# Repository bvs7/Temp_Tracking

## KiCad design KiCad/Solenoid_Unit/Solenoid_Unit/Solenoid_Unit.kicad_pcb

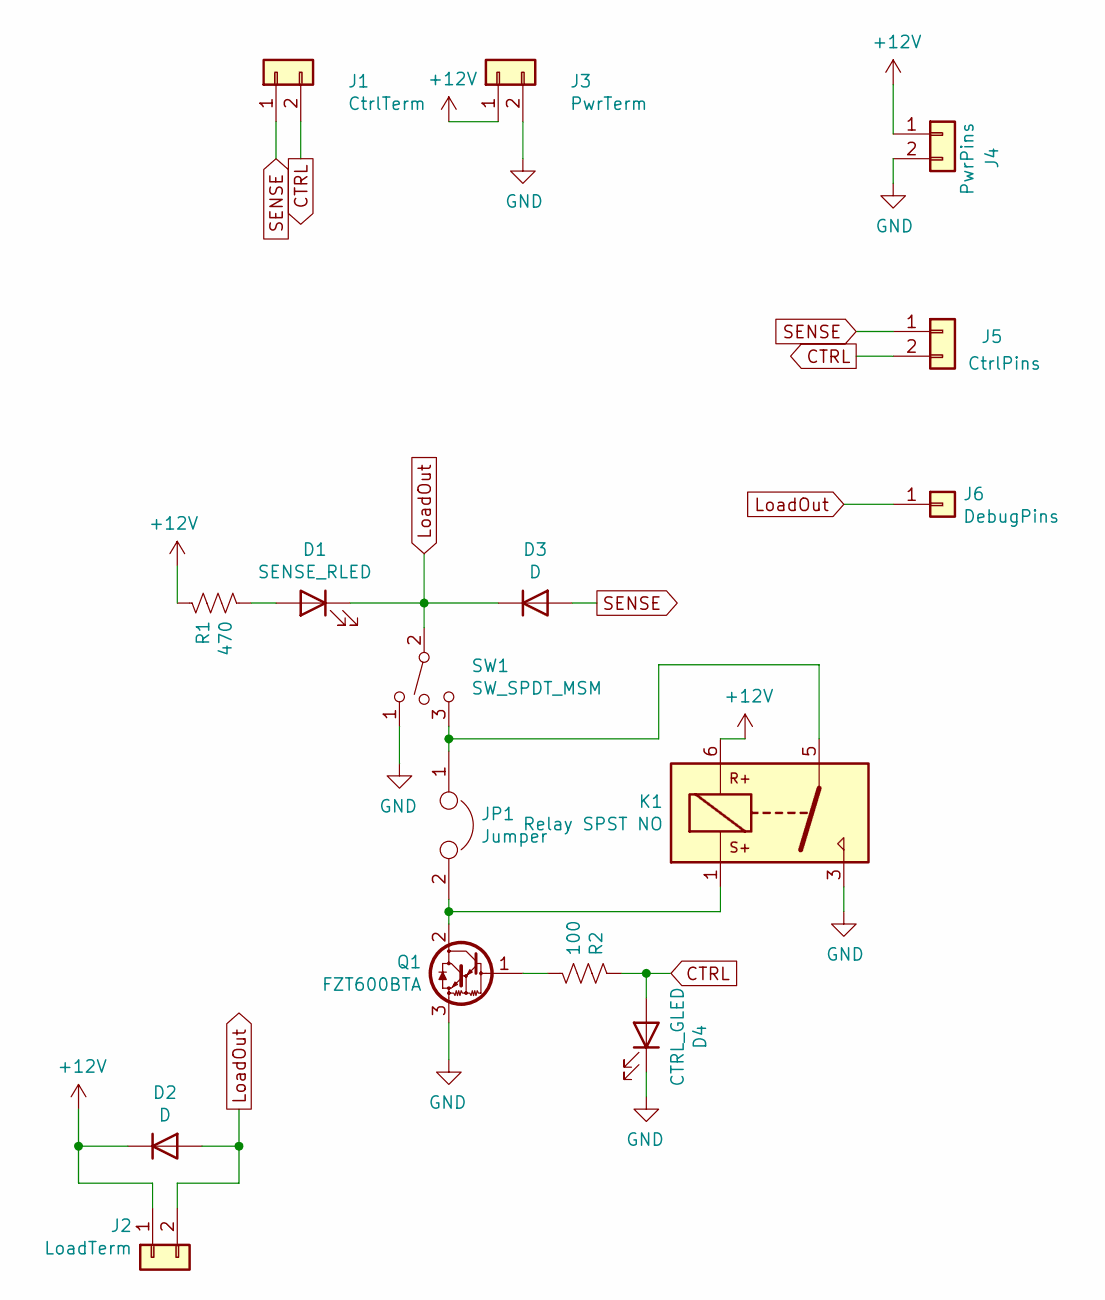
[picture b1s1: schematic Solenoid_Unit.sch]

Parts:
D1: SENSE_RLED; LED_0805_2012Metric
D2, D3: D; D_SOD-123F
D4: CTRL_GLED; LED_0603_1608Metric
J1: CtrlTerm; TerminalBlock_bornier-2_P5.08mm
J2: LoadTerm; TerminalBlock_bornier-2_P5.08mm
J3: PwrTerm; TerminalBlock_bornier-2_P5.08mm
J4: PwrPins; PinHeader_1x02_P2.54mm_Vertical
J5: CtrlPins; PinHeader_1x02_P2.54mm_Vertical
J6: DebugPins; PinHeader_1x01_P2.54mm_Vertical
JP1: Jumper; SolderJumper-2_P1.3mm_Bridged_Pad1.0x1.5mm
K1: Relay SPST NO; Relay_OMI-SH-112LM
Q1: FZT600BTA; SOT-223-3_TabPin2
R1: 470; R_0603_1608Metric
R2: 100; R_0603_1608Metric
SW1: SW_SPDT_MSM; SPDT_7101J1

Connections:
+12V: D2.1 (K), J2.1, J3.1, J4.1, K1.6, R1.1
CTRL: D4.2 (A), J1.2, J5.2, R2.1
GND: D4.1 (K), J3.2, J4.2, K1.3, Q1.3 (E), SW1.1
LoadOut: D1.1 (K), D2.2 (A), D3.1 (K), J2.2, J6.1, SW1.2
unnamed: D1.2 (A), R1.2
unnamed: JP1.1, K1.5, SW1.3
unnamed: JP1.2, K1.1, Q1.2 (C)
unnamed: Q1.1 (B), R2.2
SENSE: D3.2 (A), J1.1, J5.1

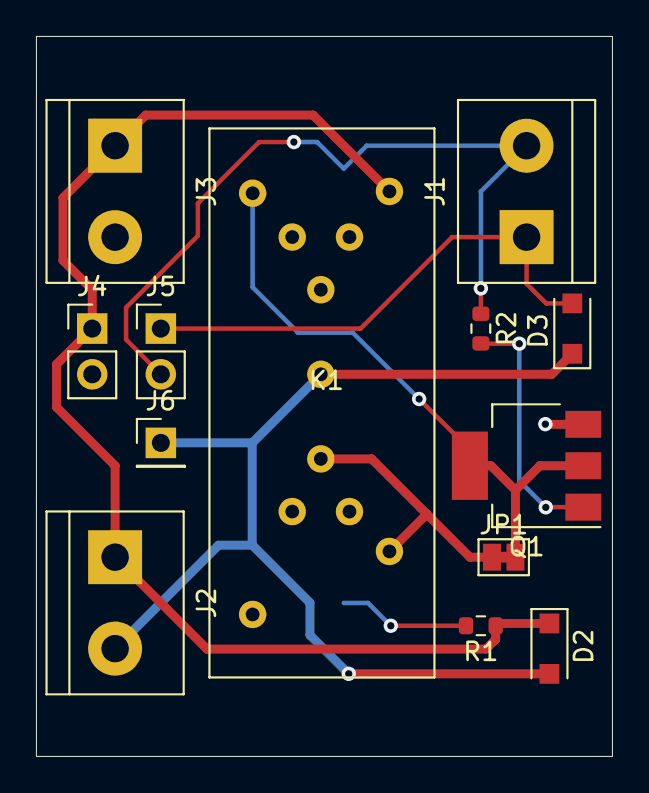
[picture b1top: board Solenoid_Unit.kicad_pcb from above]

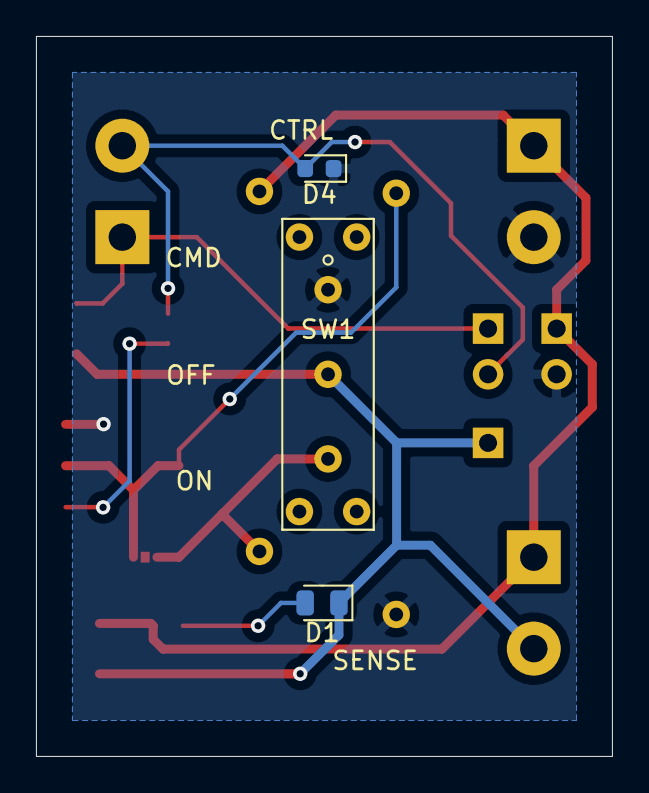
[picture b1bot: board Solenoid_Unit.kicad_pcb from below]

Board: 2 copper layers, 32.0 x 40.0 mm, 16 parts (3 on the bottom side), 9 nets.

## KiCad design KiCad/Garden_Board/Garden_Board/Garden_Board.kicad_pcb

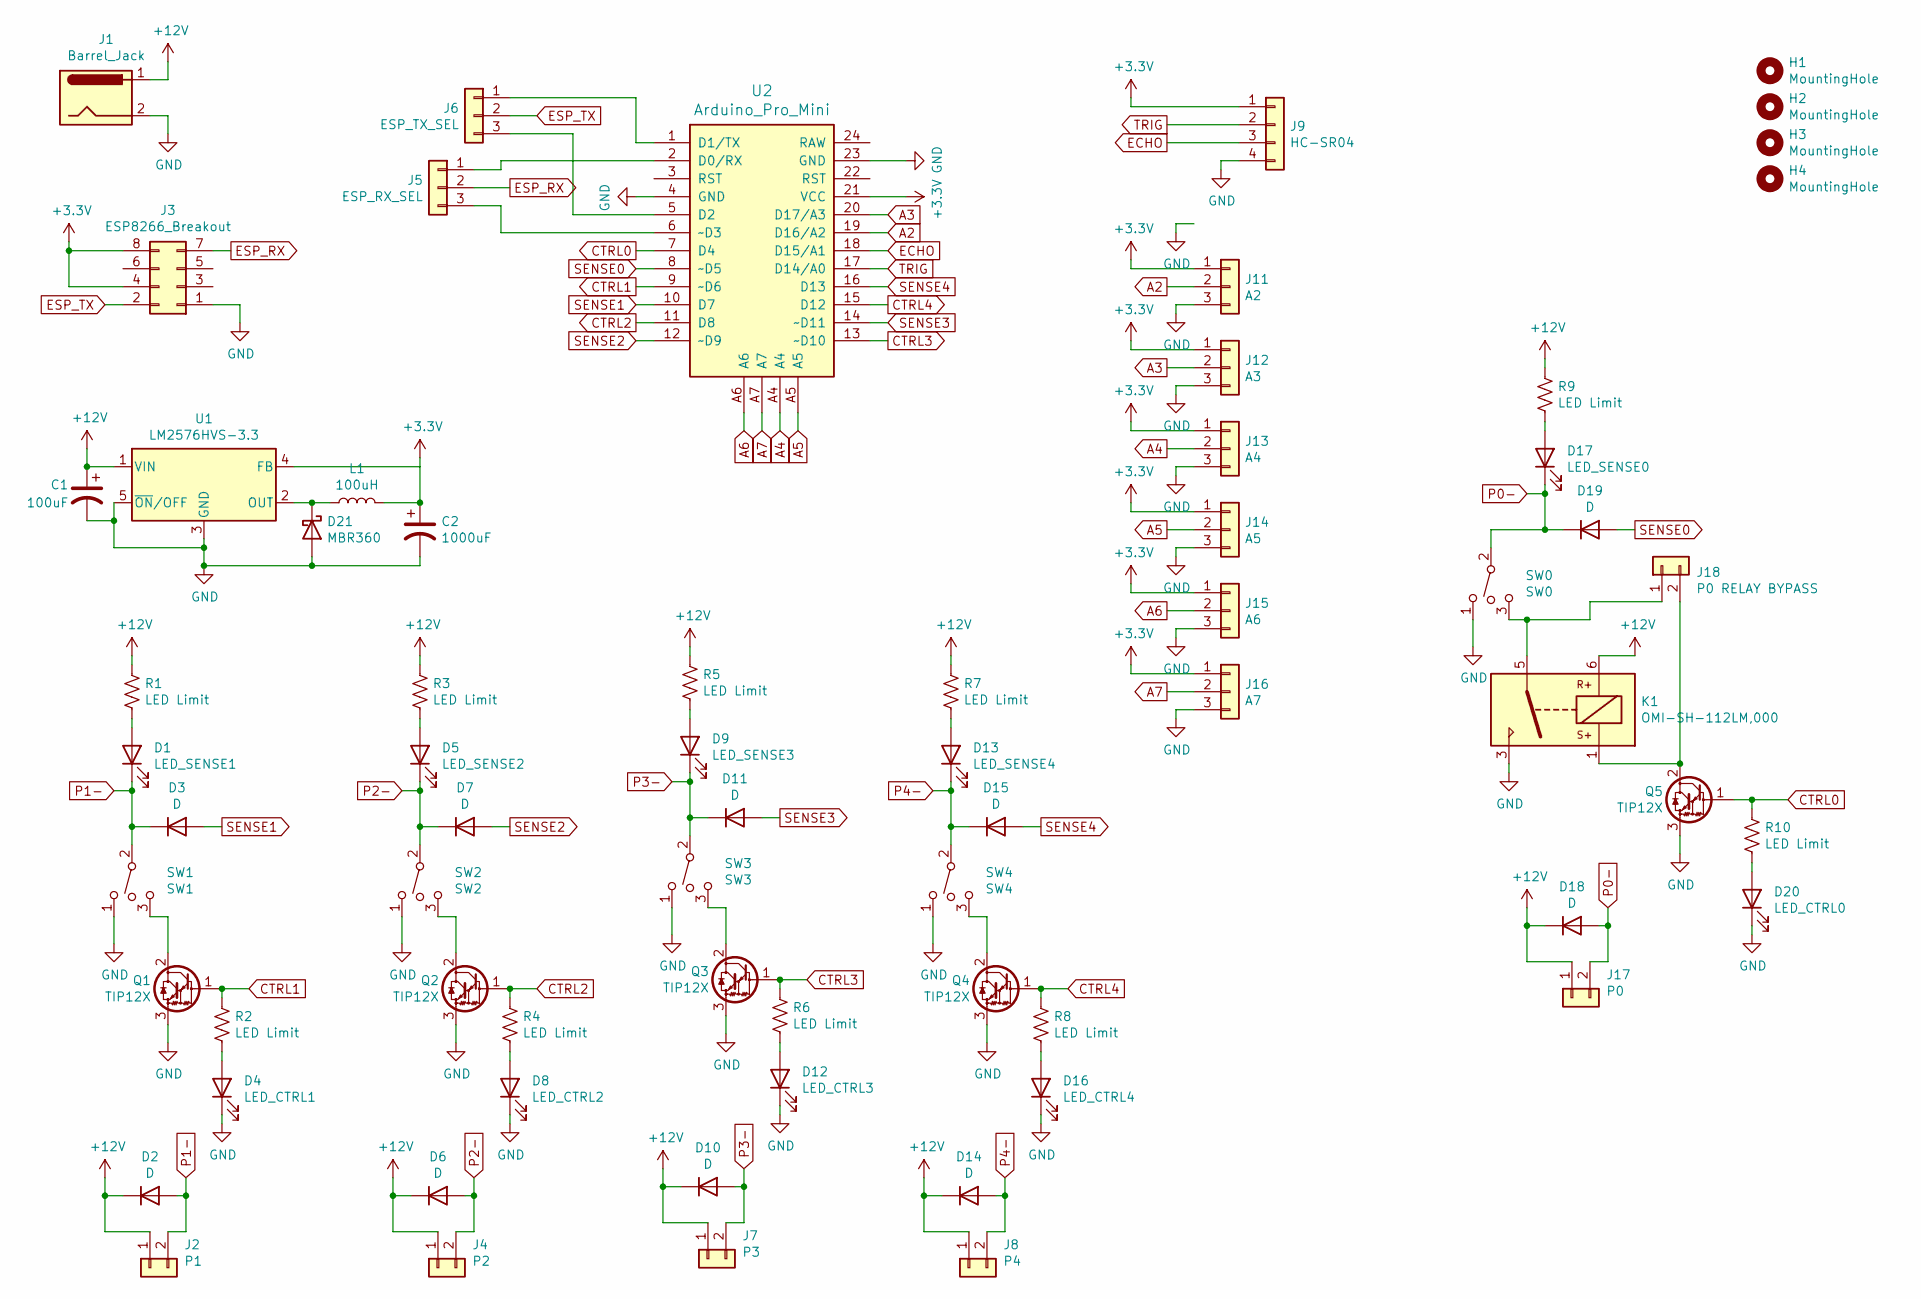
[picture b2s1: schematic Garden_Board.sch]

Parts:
C1: 100uF; CP_Radial_D5.0mm_P2.00mm
C2: 1000uF; CP_Radial_D10.0mm_P5.00mm
D1: LED_SENSE1; LED_D4.0mm
D2, D3, D6, D7, D10, D11, D14, D15, D18, D19: D; D_DO-35_SOD27_P7.62mm_Horizontal
D4: LED_CTRL1; LED_D4.0mm
D5: LED_SENSE2; LED_D4.0mm
D8: LED_CTRL2; LED_D4.0mm
D9: LED_SENSE3; LED_D4.0mm
D12: LED_CTRL3; LED_D4.0mm
D13: LED_SENSE4; LED_D4.0mm
D16: LED_CTRL4; LED_D4.0mm
D17: LED_SENSE0; LED_D4.0mm
D20: LED_CTRL0; LED_D4.0mm
D21: MBR360; D_DO-27_P12.70mm_Horizontal
H1, H2, H3, H4: MountingHole; MountingHole_3.2mm_M3
J1: Barrel_Jack; PJ-037AH_Barrel_Jack
J2: P1; TerminalBlock_bornier-2_P5.08mm
J3: ESP8266_Breakout; PinSocket_2x04_P2.54mm_Vertical
J4: P2; TerminalBlock_bornier-2_P5.08mm
J5: ESP_RX_SEL; PinHeader_1x03_P2.54mm_Vertical
J6: ESP_TX_SEL; PinHeader_1x03_P2.54mm_Vertical
J7: P3; TerminalBlock_bornier-2_P5.08mm
J8: P4; TerminalBlock_bornier-2_P5.08mm
J9: HC-SR04; PinHeader_1x04_P2.54mm_Vertical
J11: A2; PinHeader_1x03_P2.54mm_Vertical
J12: A3; PinHeader_1x03_P2.54mm_Vertical
J13: A4; PinHeader_1x03_P2.54mm_Vertical
J14: A5; PinHeader_1x03_P2.54mm_Vertical
J15: A6; PinHeader_1x03_P2.54mm_Vertical
J16: A7; PinHeader_1x03_P2.54mm_Vertical
J17: P0; TerminalBlock_bornier-2_P5.08mm
J18: P0 RELAY BYPASS; PinHeader_1x02_P2.54mm_Vertical
K1: OMI-SH-112LM,000; Relay_OMI-SH-112LM
L1: 100uH; L_Radial_D9.5mm_P5.00mm_Fastron_07HVP
Q1, Q2, Q3, Q4, Q5: TIP12X; TO-220-3_Vertical
R1, R2, R3, R4, R5, R6, R7, R8, R9, R10: LED Limit; R_Axial_DIN0207_L6.3mm_D2.5mm_P10.16mm_Horizontal
SW0: SW0; Switch_RA1153
SW1: SW1; Switch_RA1153
SW2: SW2; Switch_RA1153
SW3: SW3; Switch_RA1153
SW4: SW4; Switch_RA1153
U1: LM2576HVS-3.3; TO-220-5_Horizontal_TabDown
U2: Arduino_Pro_Mini

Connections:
+3V3: C2.1, J3.4, J3.8, J9.1, J11.1, J12.1, J13.1, J14.1, J15.1, J16.1, L1.2, U1.4 (FB), U2.21 (VCC)
+12V: C1.1, D2.1 (K), D6.1 (K), D10.1 (K), D14.1 (K), D18.1 (K), J1.1, J2.1, J4.1, J7.1, J8.1, J17.1, K1.6, R1.1, R3.1, R5.1, R7.1, R9.1, U1.1 (VIN)
A2: J11.2, U2.19 (D16/A2)
A3: J12.2, U2.20 (D17/A3)
A4: J13.2, U2.A4
A5: J14.2, U2.A5
A6: J15.2, U2.A6
A7: J16.2, U2.A7
CTRL0: Q5.1 (B), R10.1, U2.7 (D4)
CTRL1: Q1.1 (B), R2.1, U2.9 (~~D6)
CTRL2: Q2.1 (B), R4.1, U2.11 (D8)
CTRL3: Q3.1 (B), R6.1, U2.13 (~~D10)
CTRL4: Q4.1 (B), R8.1, U2.15 (D12)
ECHO: J9.3, U2.18 (D15/A1)
ESP_RX: J3.7, J5.2
ESP_TX: J3.2, J6.2
GND: C1.2, C2.2, D4.1 (K), D8.1 (K), D12.1 (K), D16.1 (K), D20.1 (K), D21.2 (A), J1.2, J3.1, J9.4, J11.3, J12.3, J13.3, J14.3, J15.3, J16.3, K1.3, Q1.3 (E), Q2.3 (E), Q3.3 (E), Q4.3 (E), Q5.3 (E), SW0.1, SW1.1, SW2.1, SW3.1, SW4.1, U1.3 (GND), U1.5 (~ON~/OFF), U2.4 (GND), U2.23 (GND)
unnamed: D1.2 (A), R1.2
unnamed: D4.2 (A), R2.2
unnamed: D5.2 (A), R3.2
unnamed: D8.2 (A), R4.2
unnamed: D9.2 (A), R5.2
unnamed: D12.2 (A), R6.2
unnamed: D13.2 (A), R7.2
unnamed: D16.2 (A), R8.2
unnamed: D17.2 (A), R9.2
unnamed: D20.2 (A), R10.2
unnamed: D21.1 (K), L1.1, U1.2 (OUT)
unnamed: J5.1, U2.2 (D0/RX)
unnamed: J5.3, U2.6 (~~D3)
unnamed: J6.1, U2.1 (D1/TX)
unnamed: J6.3, U2.5 (D2)
unnamed: J18.1, K1.5, SW0.3
unnamed: J18.2, K1.1, Q5.2 (C)
unnamed: Q1.2 (C), SW1.3
unnamed: Q2.2 (C), SW2.3
unnamed: Q3.2 (C), SW3.3
unnamed: Q4.2 (C), SW4.3
P0-: D17.1 (K), D18.2 (A), D19.1 (K), J17.2, SW0.2
P1-: D1.1 (K), D2.2 (A), D3.1 (K), J2.2, SW1.2
P2-: D5.1 (K), D6.2 (A), D7.1 (K), J4.2, SW2.2
P3-: D9.1 (K), D10.2 (A), D11.1 (K), J7.2, SW3.2
P4-: D13.1 (K), D14.2 (A), D15.1 (K), J8.2, SW4.2
SENSE0: D19.2 (A), U2.8 (~~D5)
SENSE1: D3.2 (A), U2.10 (D7)
SENSE2: D7.2 (A), U2.12 (~~D9)
SENSE3: D11.2 (A), U2.14 (~~D11)
SENSE4: D15.2 (A), U2.16 (D13)
TRIG: J9.2, U2.17 (D14/A0)

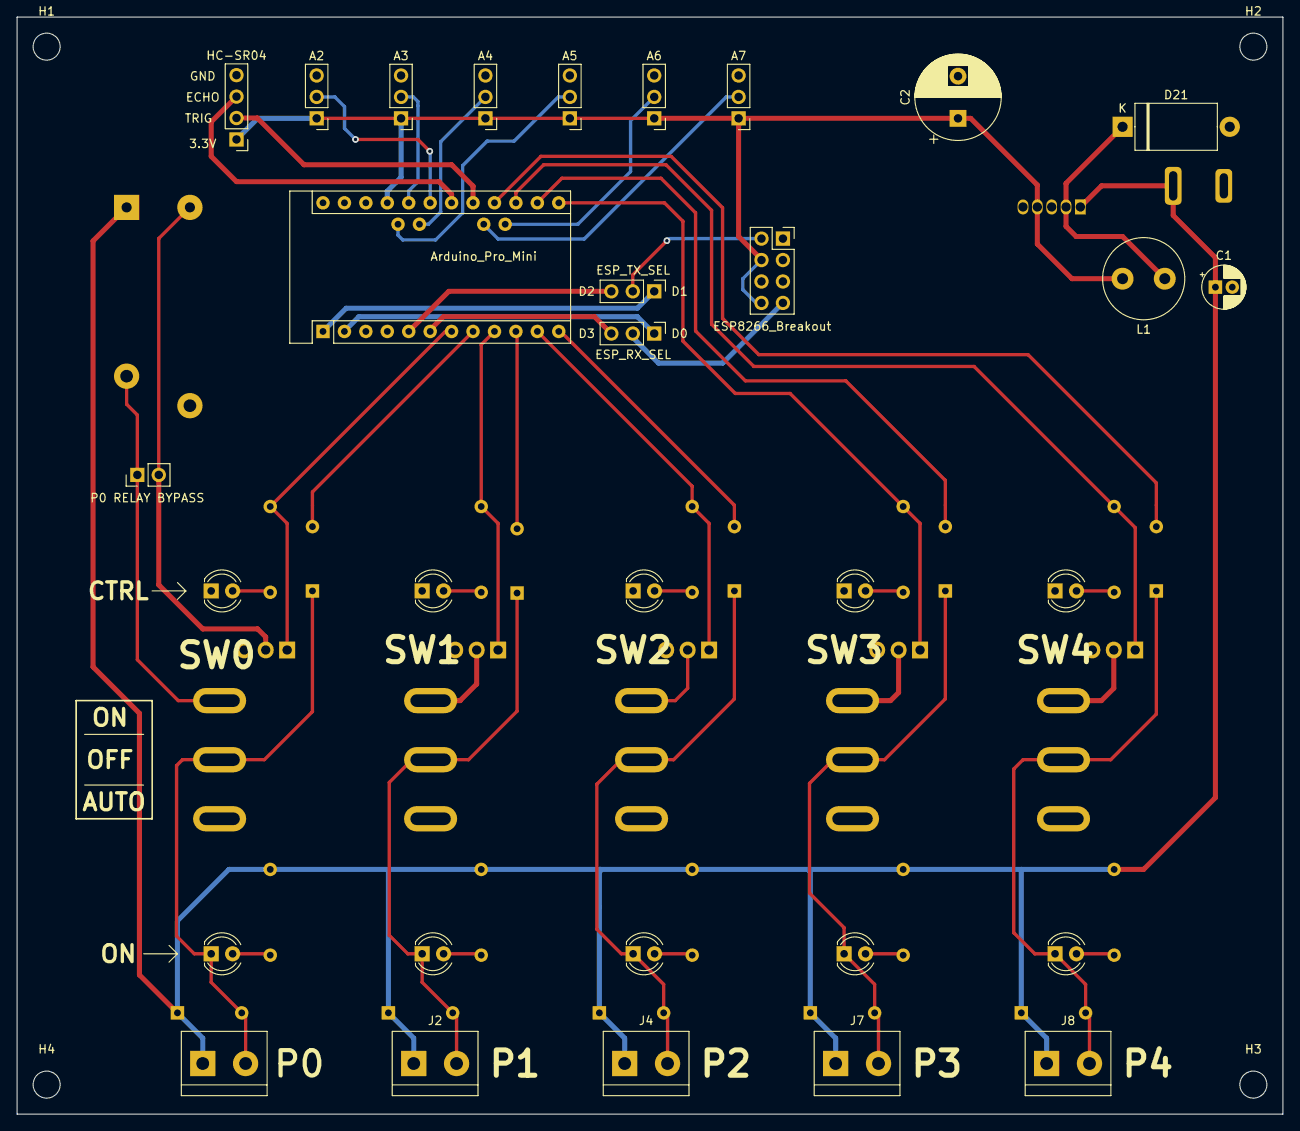
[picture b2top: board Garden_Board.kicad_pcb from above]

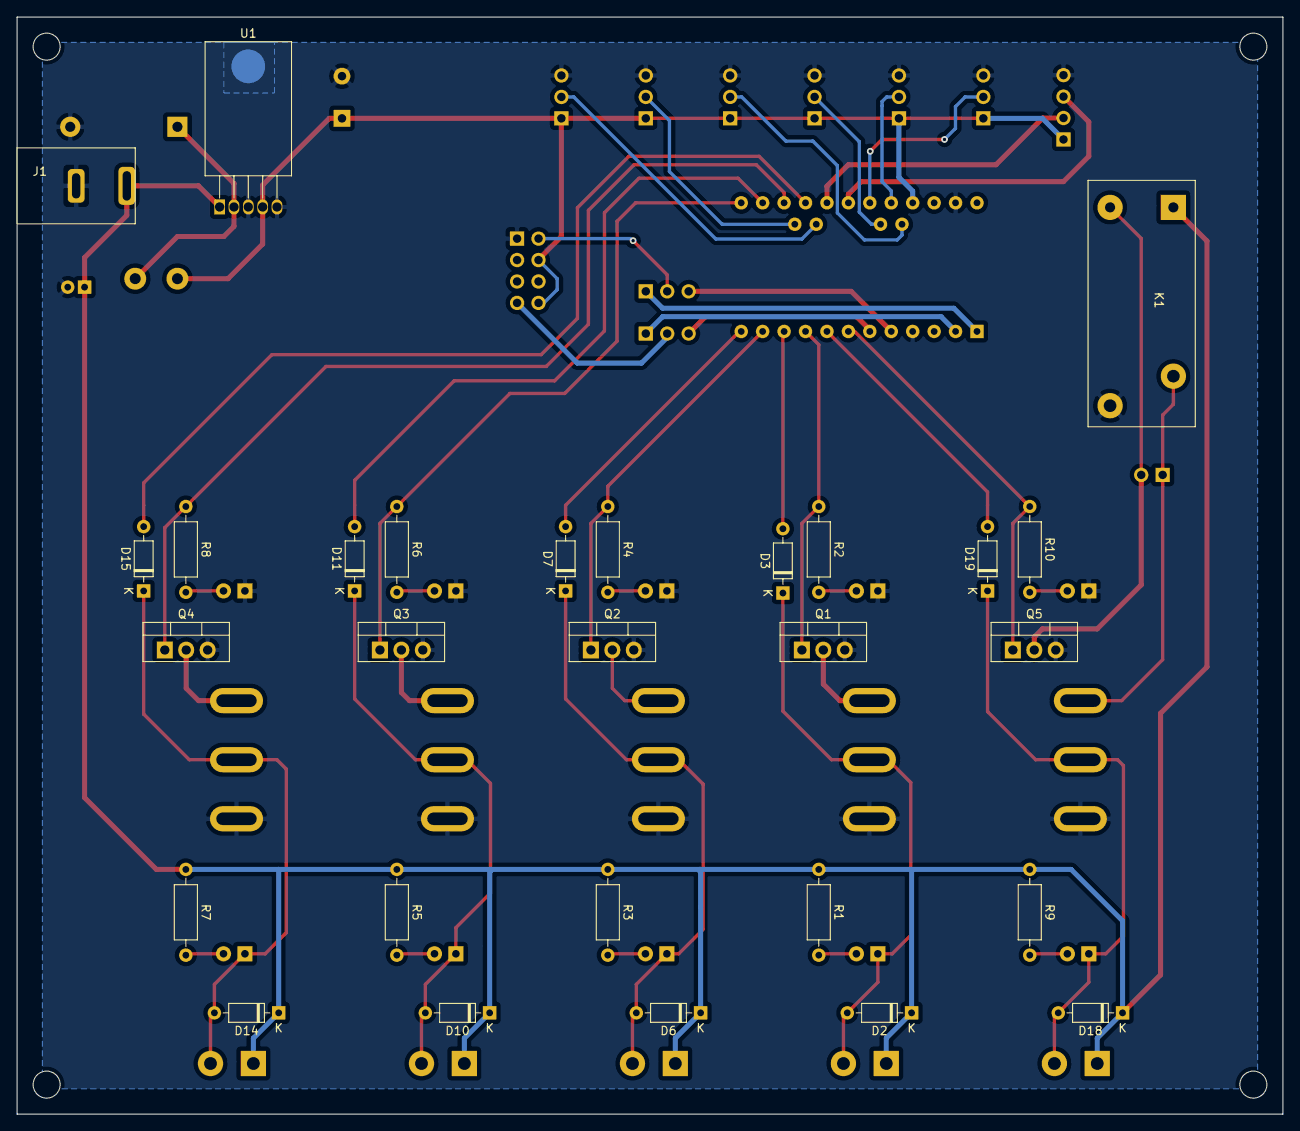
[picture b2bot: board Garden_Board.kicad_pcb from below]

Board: 2 copper layers, 150.0 x 130.0 mm, 68 parts (28 on the bottom side), 49 nets.

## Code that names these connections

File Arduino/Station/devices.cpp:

#include "devices.h"

#include "Arduino.h"
#include "connection.h"
#include "settings.h"
#include "utility.h"

unsigned long last_tick_millis = 0;
unsigned long seconds = 0;

/**
 * @brief Blocking fn to get distance from sensor.
 *
 * @return int Distance in milimeters
 */
int dist_sensor(int trig_pin, int echo_pin) {
    // Make sure that trigger pin is LOW.
    digitalWrite(trig_pin, LOW);
    delayMicroseconds(2);
    // Hold trigger for 10 microseconds, which is signal for sensor to measure
    // distance.
    digitalWrite(trig_pin, HIGH);
    delayMicroseconds(10);
    digitalWrite(trig_pin, LOW);

// Speed of sound is 343 m/s or .000343 mm/ns.
// Inverse speed of sound is 2915 ns/mm.
#define NS_PER_MM 2915
#define NS_PER_US 1000
#define MAX_DISTANCE_MM 4000
#define MAX_DURATION_US (MAX_DISTANCE_MM * 2 * NS_PER_MM / NS_PER_US)

    unsigned long duration_us = pulseIn(echo_pin, HIGH, MAX_DURATION_US);

    return (int)(duration_us * NS_PER_US / NS_PER_MM / 2);
}

/**
 * @brief Set a port to an ON/OFF ctrl state
 *
 * @param idx Port Number
 * @param set true for ON, false for OFF
 */
void p_ctrl_set(byte idx, bool set) {
    if (set) {
        digitalWrite(p[idx].ctrl, HIGH);
    } else {
        digitalWrite(p[idx].ctrl, LOW);
    }
    char topic[10] = "p0/ctrl";
    topic[1] += idx;
    publish_data(topic, set ? "true" : "false",false);
}

/**
 * @brief Check if port state has changed and update if so
 *
 * @param idx Port Number
 */
void update_p_device(uint8_t idx) {
    byte sense = p[idx].sense;
    if (sense == UNUSED_PIN) {
        return;
    }
    byte ctrl = p[idx].ctrl;
    p_state new_state = (digitalRead(sense) ? 0 : SENSE_MASK) |
                        (digitalRead(ctrl) ? CTRL_MASK : 0);
    if (p_states[idx] != new_state) {
        WARN("Update P", idx);
        WARN("", state_str[new_state]);
        p_states[idx] = new_state;
        char topic[10] = "p0/state";
        topic[1] += idx;
        char value_str[2] = "0";
        publish_data(topic, itoa(new_state,value_str,10), true);
    }
}

/**
 * @brief Update the pin modes for a port
 *      TODO: Keep track of pin use and switch duplicate pins to UNUSED_PIN
 * @param idx Port Number
 */
void p_device_setup(uint8_t idx) {
    VERBOSE("Setting up P", idx);
    byte sense = p[idx].sense;;
    if (sense == UNUSED_PIN) {
        return;
    }
    byte ctrl = p[idx].ctrl;
    // TODO: check pin conflicts
    pinMode(sense, INPUT);
    pinMode(ctrl, OUTPUT);
    digitalWrite(ctrl, p_states[idx] & CTRL_MASK);
    p_states[idx] |= P_REQUEST_FLAG;
}

void homie_setup(char *category, char *station_name){

    char topic[40]; // topic: "homie/device_id/"
    snprintf(topic, 40, "%s/%s/", category, station_name);
    char *setting = topic + strlen(topic);
    publish_homie_sett(topic, setting, "$homie", "4.0.0");
    publish_homie_sett(topic, setting, "$state", "init");
    publish_homie_sett(topic, setting, "$name", station_name);

    char nodes[32] = {0};
    bool first = true;
    for(int i=0; i < NUM_P_DEVICES; i++){
        if(p[i].sense != UNUSED_PIN){
            char node[4] = "p0";
            node[1] += i;
            if(first){
                first = false;
            } else {
                strcat(nodes, ",");
            }
            strcat(nodes, node);
        }
    }

    publish_homie_sett(topic, setting, "$nodes", nodes);
    publish_homie_sett(topic, setting, "$extensions", "");

    for(uint8_t i=0; i<5; i+=1){
        if(p[i].sense == UNUSED_PIN){
            continue;
        }
        char node[4] = "p0"; // Extra space for '/'
        node[1] += i;
        if (i == 0){
            homie_pnode_setup(node, topic, setting, "pump");
        }else{
            homie_pnode_setup(node, topic, setting, "valve");
        }
    }

    publish_homie_sett(topic, setting, "$state", "ready");
}

void homie_pnode_setup(char *n_id, char *topic, char *sett, char *n_type){

    strcpy(sett, n_id); // topic: "homie/device_id/pN"
    char *n_setting = topic + strlen(topic);
    strcpy(n_setting, "/");   // topic: "homie/device_id/pN/"
    n_setting = topic + strlen(topic);
    publish_homie_sett(topic, n_setting, "$name", n_id);
    publish_homie_sett(topic, n_setting, "$type", n_type);
    publish_homie_sett(topic, n_setting, "$properties", "ctrl,state");

    strcpy(n_setting, "ctrl/"); // topic: "homie/device_id/pN/ctrl/"
    char *p_setting = topic + strlen(topic);
    publish_homie_sett(topic, p_setting, "$name", "ctrl");
    publish_homie_sett(topic, p_setting, "$datatype", "boolean");
    publish_homie_sett(topic, p_setting, "$settable", "true");

    strcpy(n_setting, "state/"); // topic: "homie/device_id/pN/state/"
    p_setting = topic + strlen(topic);
    publish_homie_sett(topic, p_setting, "$name", "state");
    publish_homie_sett(topic, p_setting, "$datatype", "integer");
    publish_homie_sett(topic, p_setting, "$format", "0:7");

    strcpy(sett, ""); // Reset topic to "homie/device_id/"
}

void publish_homie_sett(char *base_topic, char *sett_loc,
                        const char *sett_name, const char *sett_value){
    strcpy(sett_loc, sett_name);
    publish(base_topic, sett_value, true);
    mqtt_client.loop();
}

/**
 * @brief Set up Devices. Port sense/ctrl and sensor input/trig pins
 */
void devices_setup() {
    VERBOSE("Devices setup", "");

    homie_setup(category, station_name);
    // Reset pin conflicts
    // TODO: Consider conflicts from utility.h, LED_PIN and DEBUG_LED_ENABLE
    for (uint8_t i = 0; i < NUM_P_DEVICES; i++) {
        p_device_setup(i);
    }


    last_tick_millis = millis();

    Serial.println("Setup complete");
}

void sec_loop(unsigned long seconds) {
    for (uint8_t i = 0; i < NUM_P_DEVICES; i++) {
        update_p_device(i);
    }

}

/**
 * @brief Update devices
 *      Upon a one second tick,
 *          Check for poll_interval and update all sensors if needed
 *          Check for port updates
 *          Check for sensor update requests
 */
void devices_loop() {
    VERBOSE2("Devices loop", "");
    unsigned long current_millis = millis();
    if (current_millis - last_tick_millis > SEC) {
        VERBOSE("Tick ", seconds);
        dot();
        sec_loop(seconds);
        seconds += 1;
        while (current_millis - last_tick_millis > SEC) {
            last_tick_millis += SEC;
        }
    }
}

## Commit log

2021-08-27 Rename README.md to Nest_Handler/README.md
2021-08-27 Add some documentation
2021-08-27 typo
2021-08-27 Add todo
2021-08-27 Add Raised Beds Todo list
2021-08-27 Add KiCad files
2021-08-31 Add Arduino and configure vscode for arduino
2021-09-01 python mqtt testing
2021-09-01 Testing MQTT
2021-09-02 Mostly finished MQTT Subscriber Database Manager
2021-09-02 Start on Flask Webserver
2021-09-03 Add Web Display Basics
2021-09-03 Debug webserver
2021-09-04 Add Templates. Change database table names
2021-12-22 Home update
2021-12-22 Reorganize modules
2022-08-01 Working Serial/MQTT connections
2022-08-03 Update gitignore
2022-08-03 Update to work with VS code at work
2022-08-03 Add devices and device commands
2022-08-04 Try to overhaul SerialCommands:
2022-08-04 Overhaul
2022-09-11 Update Board V2 Darlington pair transistors for more current at ports, switching power supply for efficiency
2022-09-11 Multiple reworks. Going for simplicity now
2022-09-12 Everything working except mqtt
2022-09-12 Test and finish mqtt callback
2022-09-12 Clean up error reporting to use less memory
2022-09-14 Documentation/Protocol updates and simplification
2022-09-14 Forgot one file
2022-09-14 Make station name unwritable, and add FW Version check
2022-09-14 Add category to mqtt, needs testing
2022-09-14 GardenDeviceDataListener Implementation
2022-09-15 Debug on Pi
2022-09-16 Refine UX
2022-09-16 Refactor GardenDataHandler and add functionality
2022-09-16 Add flutter app
2022-09-16 Start backend server
2022-09-16 Clean up documentation
2022-09-16 Docs update
2022-09-18 Debug station
2022-09-18 workspace
2022-09-20 Sync
2022-09-21 Add homie implementation
2022-09-24 Homie station debugging
2022-12-08 Mini Solenoid Unit
2022-12-10 Testing wifi
2022-12-10 Major debugging and issues. Going to try simplifiying
